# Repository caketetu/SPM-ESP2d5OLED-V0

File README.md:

# SPM-STMTB-LVSD

## 概要

ESP32を使用した3.2inchLCDディスプレイ制御ボード\
LCDの裏側にコンパクトに装着できる。LCDディスプレイは秋月で購入。\
https://akizukidenshi.com/catalog/g/g116265/

## 機能

* ステッピングモーターの定電流制御
* 速度制御モード、位置制御モード
* 自動加減速制御
* RS485,CANインターフェース
* Enable信号入力
* リミットセンサーによる原点復帰、リミット停止
* エンコーダー入力による脱調検知 

## ピンアサイン
| Function       | Pin  | 備考 |
| -------------- | ---- | ---- |
| TIM2_CH1       | PA0  |   ENC-A   |
| TIM2_CH2       | PA1  |   ENC-B   |
| USART2_TX      | PA2  |   SYS-RS485   |
| GPIO_Input     | PA3  |   H_LIMIT   |
| GPIO_Input     | PA4  |   L_LIMIT   |
| SPI1_SCK       | PA5  |   SYS-SPI   |
| SPI1_MISO      | PA6  |   SYS-SPI   |
| SPI1_MOSI      | PA7  |   SYS-SPI   |
| TIM1_CH1       | PA8  |  CK    |
| USART1_TX      | PA9  |  SYS-UART    |
| USART1_RX      | PA10 |  SYS-UART    |
| FDCAN1_RX      | PA11 |  SYS-CANFD    |
| FDCAN1_TX      | PA12 |  SYS-CANFD    |
| DEBUG_SWDIO    | PA13 |  SYS-DEBUG    |
| DEBUG_SWCLK    | PA14 |  SYS-DEBUG    |
| USART2_RX      | PA15 |  SYS-RS485    |
| SPI1_NSS       | PB0  |  SYS-SPI    |
| GPIO_Output    | PB1  |  STBY    |
| GPIO_Output    | PB2  |  CW/CCW    |
| GPIO_Output    | PB3  |  M1    |
| GPIO_Output    | PB4  |  SYS-LED1    |
| GPIO_Input     | PB5  |  SYS-EN    |
| GPIO_Output    | PB6  |  M2    |
| GPIO_Output    | PB7  |  ENABLE    |
| GPIO_Output    | PB8  |  TQ    |
| GPIO_Input     | PB9  |   HOME   |
| GPIO_Output    | PC6  |   SYS-LED0    |
| RCC_OSCIN      | PC14 |   SYS-CLOCK   |
| RCC_OSCOUT     | PC15 |   SYS-CLOCK   |
| RCC_MCO        | PF2  |   SYS-DEBUG   |

※SYS-はSPM共通インターフェース

## 開発環境

| 項目       | 内容                      |
| -------- | ----------------------- |
| MCU      | STM32C092KBT6           |
| IDE      | STM32CubeIDE for VSCode |
| CubeMX   | STM32CubeMX 6.15.0      |
| Firmware | STM32CubeC0             |
| Language | C                       |

## 実装予定機能

* [ ] CAN通信
* [ ] リミット検知
* [ ] 原点復帰
* [ ] エンコーダー脱調検知

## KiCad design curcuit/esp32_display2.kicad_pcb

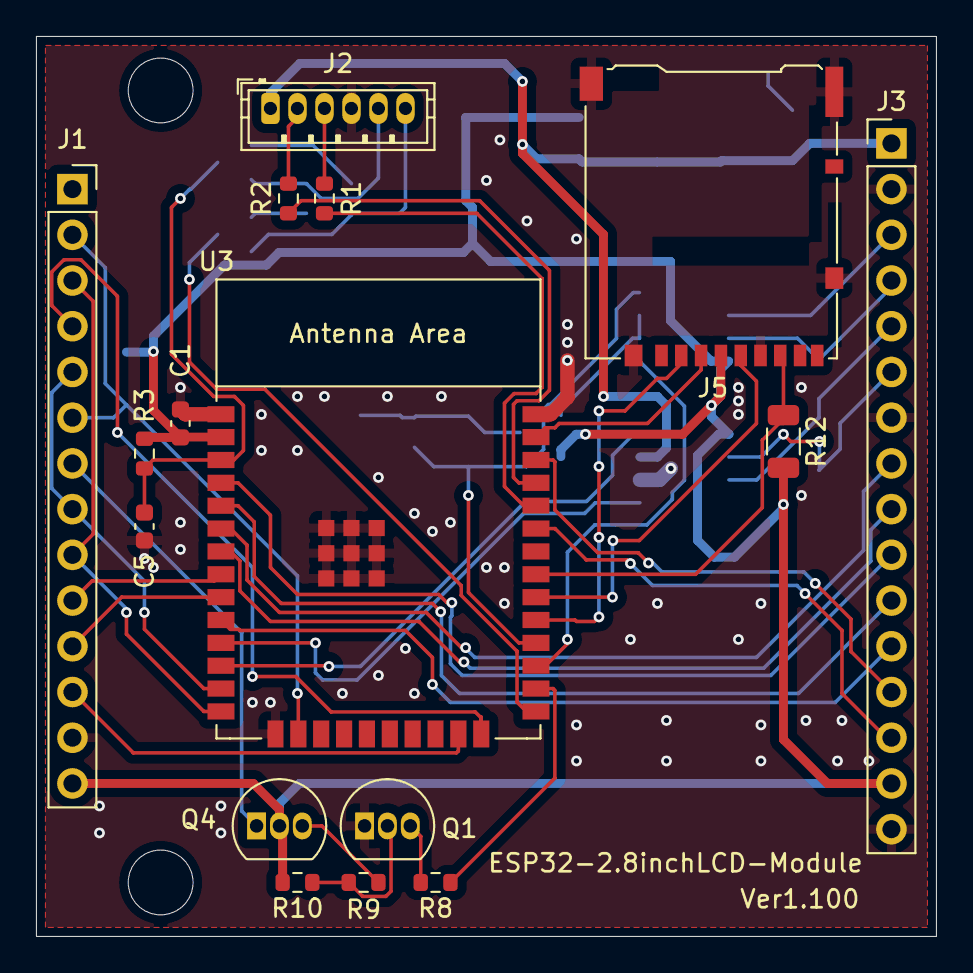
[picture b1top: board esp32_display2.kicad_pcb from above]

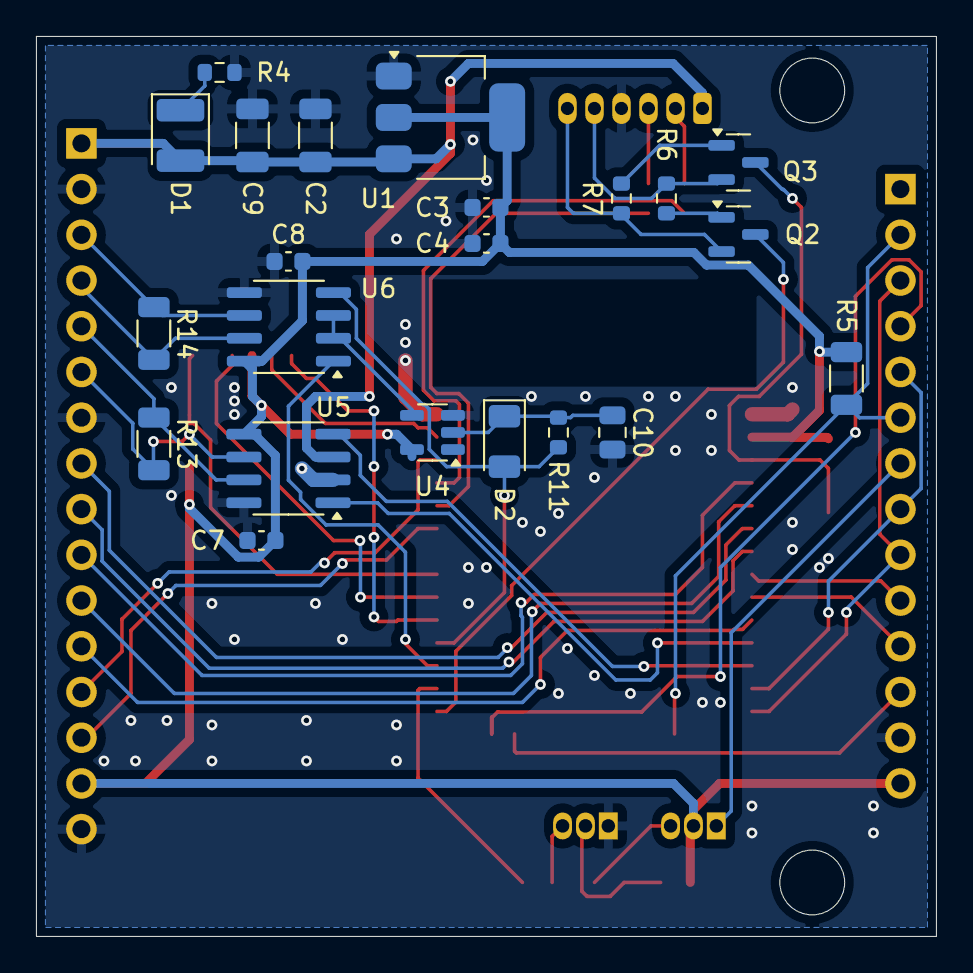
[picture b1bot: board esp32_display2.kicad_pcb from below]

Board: 2 copper layers, 50.0 x 50.0 mm, 38 parts (22 on the bottom side), 33 nets.

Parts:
C1, C5, C7, C8: C0.1u; C_0603_1608Metric
C2, C9: C10u; C_1206_3216Metric
C3, C4: C10u; C_0603_1608Metric
C10: C0.01u; C_0805_2012Metric
D1: LED; LED_1210_3225Metric
D2: D; D_1206_3216Metric
J1: Conn_01x14_Pin; PinSocket_1x14_P2.54mm_Vertical
J2: Conn_01x06_Pin; JST_ZH_B6B-ZR_1x06_P1.50mm_Vertical
J3: Conn_01x16_Pin; PinHeader_1x16_P2.54mm_Vertical
J5: Micro_SD_Card_Det_Hirose_DM3AT; microSD_HC_Hirose_DM3AT-SF-PEJM5
Q1: 2SC1815; TO-92_Inline
Q2, Q3: DTC114E; SOT-23
Q4: 2SA1015; TO-92_Inline
R1, R2, R4, R8, R9, R10: R1k; R_0603_1608Metric
R3, R6, R7, R11: R10k; R_0603_1608Metric
R5, R12: R10k; R_1206_3216Metric
R13: R150; R_1206_3216Metric
R14: R120; R_1206_3216Metric
U1: LD1117S33TR_SOT223; SOT-223-3_TabPin2
U3: ESP32-WROOM-E; ESP32-WROOM-32E
U4: 74LVC1G14; SOT-23-5
U5: MCP2562-E-SN; SOIC-8_3.9x4.9mm_P1.27mm
U6: MAX3485; SOIC-8_3.9x4.9mm_P1.27mm

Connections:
+3V3: C1.1, C3.1, C4.1, C7.1, C8.1, J1.14, J3.15, J5.4 (VDD), Q4.2 (C), R3.1, R5.2, R10.2, R12.2, U1.2 (VO), U3.2 (3V3), U4.5 (VCC), U5.5 (Vio), U6.8 (VCC)
+5V: C2.1, C9.1, D1.2 (A), J2.1, J3.1, U1.3 (VI), U5.3 (VDD)
BOOT: Q2.3 (C), U3.25 (GPIO0/BOOT/ADC2_CH1)
CANH: J3.5, R13.1, U5.7 (CANH)
CANL: J3.6, R13.2, U5.6 (CANL)
DTR: J2.6, Q2.2 (E), R7.1
EN: C5.1, Q3.3 (C), R3.2, U3.3 (EN/CHIP_PU)
GND: C1.2, C2.2, C3.2, C4.2, C5.2, C7.2, C8.2, C9.2, C10.2, J1.13, J2.4, J3.2, J3.7, J3.16, J5.6 (VSS), J5.11 (SHIELD), Q1.1 (E), R4.2, U1.1 (GND), U3.1 (GND), U3.15 (GND), U3.38 (GND), U3.39 (GND_THERMAL), U4.3 (GND), U5.2 (VSS), U5.8 (STBY), U6.5 (GND)
IO0: J3.8, U3.6 (GPIO34/ADC1_CH6)
IO1: J3.9, U3.7 (GPIO35/ADC1_CH7)
IO2: J3.10, U3.4 (SENSOR_VP/GPIO36/ADC1_CH0)
IO3: J3.11, U3.5 (SENSOR_VN/GPIO39/ADC1_CH3)
IO4: J3.12, U3.10 (DAC_1/ADC2_CH8/GPIO25)
IO5: J3.13, U3.36 (GPIO22)
IO6: J3.14, U3.33 (GPIO21)
RE_DE: U4.4, U6.2 (~RE), U6.3 (DE)
RS485+: J3.3, R14.1, U6.6 (A)
RS485-: J3.4, R14.2, U6.7 (B)
RTS: J2.5, Q3.2 (E), R6.1
RXD: J2.3, R1.2
TXD: J2.2, R2.2
cs: J1.12, U3.23 (MTDO/GPIO15/ADC2_CH3)
dc: J1.10, U3.8 (32K_XP/GPIO32/ADC1_CH4)
led: R8.1, U3.26 (ADC2_CH0/GPIO4)
reset: J1.11, U3.9 (32K_XN/GPIO33/ADC1_CH5)
sck: J1.5, J1.8, U3.13 (MTMS/GPIO14/ADC2_CH6)
sd_cs: J5.2 (DAT3/CD), U3.29 (GPIO5)
sd_miso: J5.7 (DAT0), R12.1, U3.31 (GPIO19)
sd_mosi: J5.3 (CMD), U3.37 (GPIO23)
sd_sck: J5.5 (CLK), U3.30 (GPIO18)
sdi: J1.3, J1.9, U3.14 (MTDI/GPIO12/ADC2_CH5)
sdo: J1.2, J1.6, R5.1, U3.16 (MTCK/GPIO13/ADC2_CH4)
t_cs: J1.4, U3.24 (ADC2_CH2/GPIO2)
